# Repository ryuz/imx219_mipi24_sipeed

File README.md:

# Tang Mega 138K Pro Dock 用 IMX219 MIPI 変換基板

[English version is here (README_en.md)](README_en.md)

## 概要

[Raspberry Pi Camera V2](https://raspberry-pi.ksyic.com/main/index/pdp.id/144/pdp.open/144) のベース基板を入れ替えて、Sipeed さんの [Tang Mega 138K Pro Dock](https://wiki.sipeed.com/hardware/en/tang/tang-mega-138k/mega-138k-pro.html) に繋ぐための変換基板です。

おそらく Sipeed さんの独自仕様と思われる 24pin の MIPI コネクタで Sonyさんの IMX219 センサーを利用可能にします。

## 変換基板のイメージ

下記のような変換基板です。

Raspberry Pi Camera V2 カメラから、カメラモジュール部分を取り外して、この変換基板に取り付けることで、利用します。

実際に取り付けたのが下記の写真です。

## 各種データ

回路図は下記の通りです(pdf版は[こちら](imx219_mipi24/imx219_mipi24.pdf))です。

[KiCAD](https://www.kicad.org/) version 9.0.0 で設計しております。

[JLCPCB](https://jlcpcb.com/) さんの４層基板で「FR4-Standard TG 135-140」の製造仕様に合わせてインピーダンスコントロールしております。

手元での試作は JLCPCBさんの PCBA で行っており、たまたま在庫表示のあった部品を選定したこともあり、発信器などでディスコン品番なども混ざっておりますが、各自で製造される場合は必要に応じて後継の互換品を選定ください。

ケーブルは[05-24-A-0030-A-4-06-4-T](https://www.marutsu.co.jp/pc/i/46064636/) と [05-24-A-0152-A-4-06-4-T](https://www.marutsu.co.jp/pc/i/46064715/) の2種類で試しております。

## 動作テスト

下記のプロジェクトなどで動作テストを行っております。

- https://github.com/ryuz/jelly/tree/master/projects/tang_mega_138k_pro/tang_mega_138k_pro_imx219_720p
- https://github.com/ryuz/jelly/tree/master/projects/tang_mega_138k_pro/tang_mega_138k_pro_imx219_stereo

実際に2つのカメラを繋いで、256x256 の画像を交互に表示したいるのが下記です。

なお単純な受信テストは 2lane と 4lane の両方ともうまくいっております。

## 免責事項

本設計データは、研究開発用の試作実験に用するものであり、利用に際して発生した如何なる損害も作者は補償いたしませんので予めご了承ください。

## BOOTH への出品

自身で基板製造するのが難しい方の為に、作者が少し余分に製造したものを [BOOTH](https://rtc-lab.booth.pm/) に出品しております。

- [Tang Mega 138K Pro Dock 用 IMX219 MIPI 変換基板](https://rtc-lab.booth.pm/items/7095235)
- [Tang Mega 138K Pro Dock 用 IMX219 MIPI カメラ基板(イメージセンサー付き)](https://rtc-lab.booth.pm/items/7132890)

あくまで試作品ですので品質を保証できるものではなく、在庫限りとなりますが、よろしければご活用ください。

当方からご購入いただいた基板に関しては商用/非商用ともに自由にお使いいただけます。
購入品の商用利用の為に回路図のみ別途[こちら](https://github.com/ryuz/imx219_mipi24_sipeed_schematic)でMITライセンスでも公開しております。

## ライセンス(License)

本設計データは、[クリエイティブ・コモンズ 表示-非営利 4.0 国際 ライセンス](https://creativecommons.org/licenses/by-nc/4.0/deed.ja)の下で提供されています。

製造した本基板の販売や配布を行わない限りは、趣味や研究開発用途でご自由にお使いいただく事が出来ます。
また、商用に製造販売を希望される場合は、別途ライセンス契約を作者までご相談ください。

## 作者情報

渕上 竜司(Ryuji Fuchikami)
[リアルタイムコンピューティング研究所](https://rtc-lab.com/)

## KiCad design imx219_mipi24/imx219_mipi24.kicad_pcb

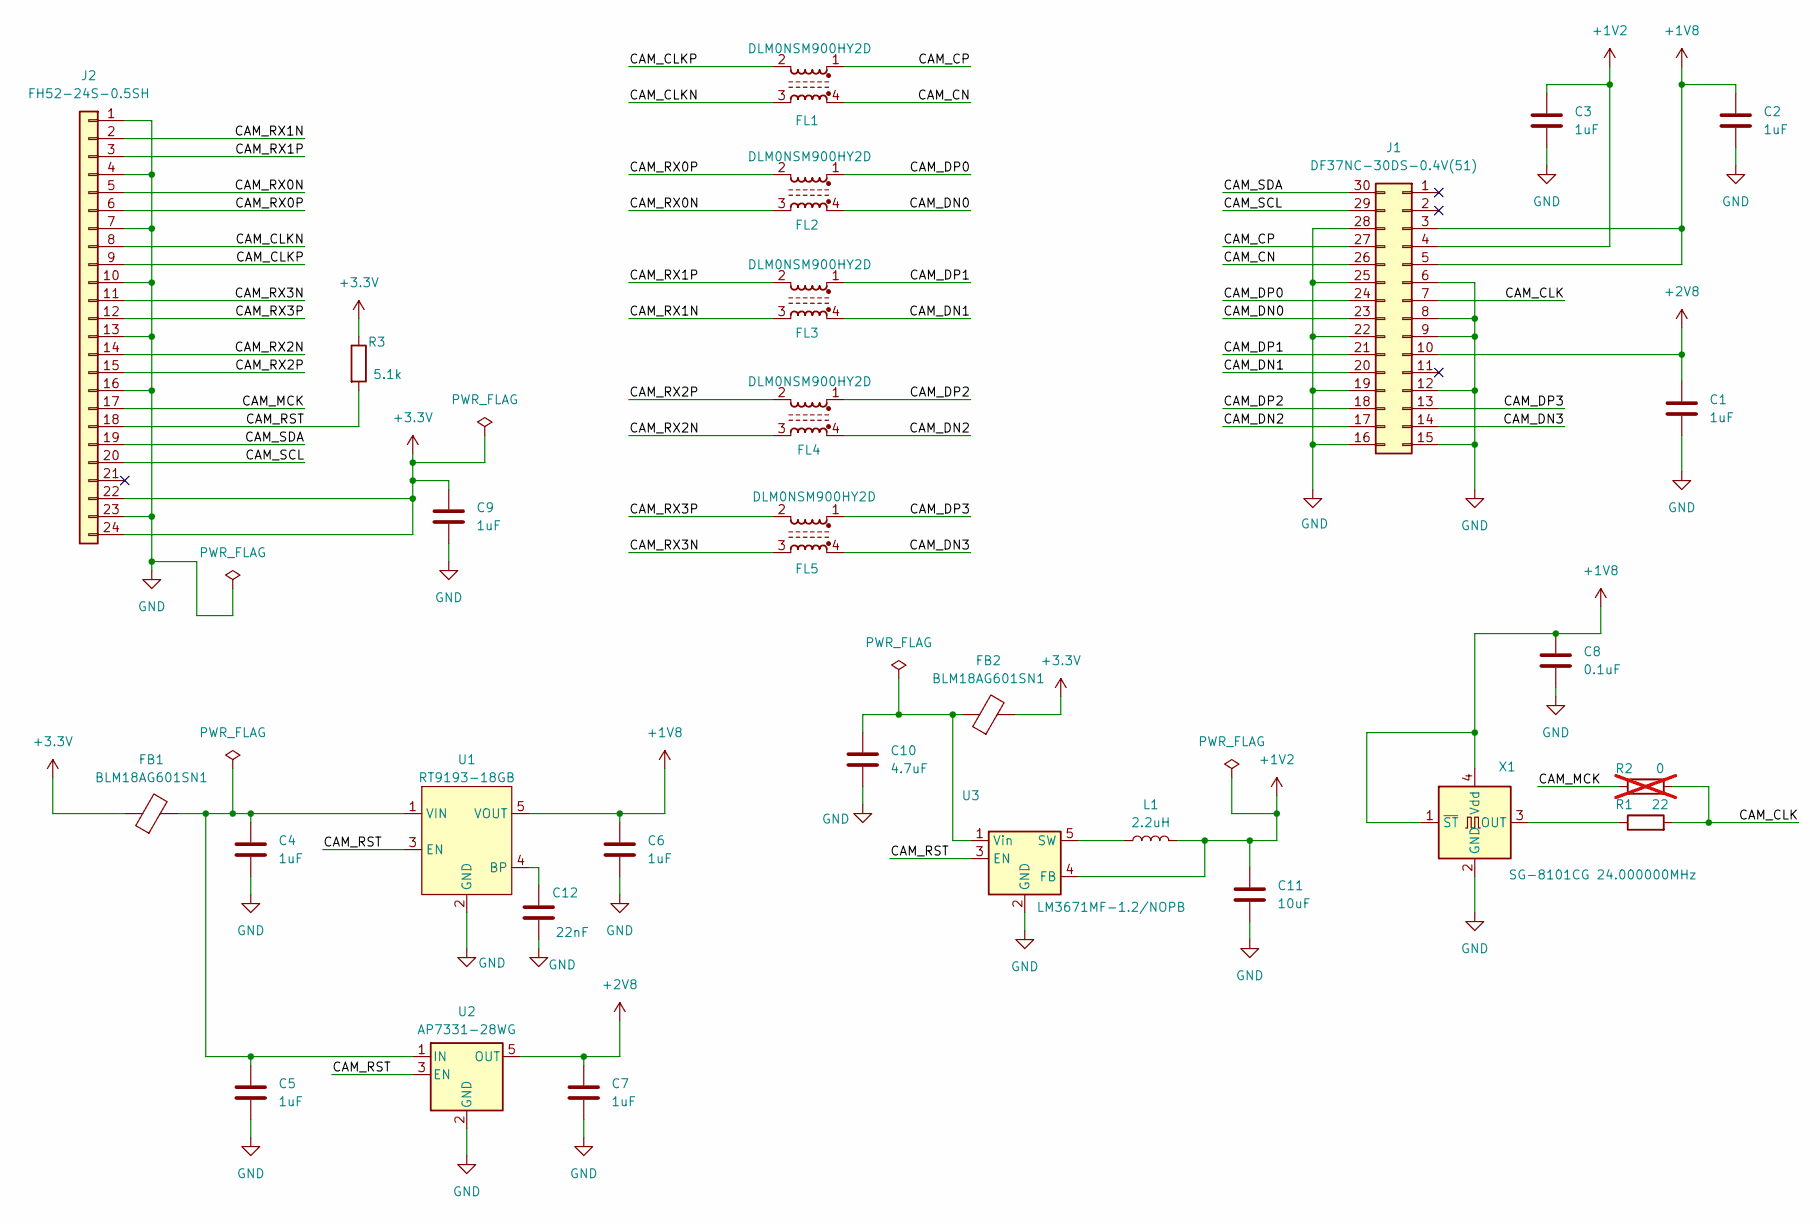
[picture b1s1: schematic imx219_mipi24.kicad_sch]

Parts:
C1, C2, C3, C4, C5, C6, C7, C9: 1uF; C_0402_1005Metric
C8: 0.1uF; C_0402_1005Metric
C10: 4.7uF; C_0603_1608Metric
C11: 10uF; C_0603_1608Metric
C12: 22nF; C_0402_1005Metric
FB1, FB2: BLM18AG601SN1; L_0603_1608Metric; JLC C19330
FL1, FL2, FL3, FL4, FL5: DLM0NSM900HY2D; JLC C1857796
J1: DF37NC-30DS-0.4V(51); HRS_DF37NC-30DS-0.4V_51; JLC C424634
J2: FH52-24S-0.5SH; JLC C5378714
L1: 2.2uH; L_1008_2520Metric; JLC C5832372
R1: 22; R_0402_1005Metric
R2: 0; R_0402_1005Metric; not fitted
R3: 5.1k; R_0402_1005Metric
U1: RT9193-18GB; SOT-23-5; JLC C27416
U2: AP7331-28WG; SOT25; JLC C460376
U3: LM3671MF-1.2/NOPB; TSOT-23-5; JLC C2650333
X1: SG-8101CG 24.000000MHz; SG-8101CG; JLC C390546

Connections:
+1V2: C3.1, C11.1, J1.4, L1.2, U3.4 (FB)
+1V8: C2.1, C6.1, C8.1, J1.3, J1.5, U1.5 (VOUT), X1.1 (~ST), X1.4 (Vdd)
+2V8: C1.1, C7.1, J1.10, U2.5 (OUT)
+3.3V: C9.1, FB1.1, FB2.2, J2.22, J2.24, R3.1
/CAM_CLK: J1.7, R1.2, R2.2
/CAM_CLKN: FL1.3, J2.8
/CAM_CLKP: FL1.2, J2.9
/CAM_CN: FL1.4, J1.26
/CAM_CP: FL1.1, J1.27
/CAM_DN0: FL2.4, J1.23
/CAM_DN1: FL3.4, J1.20
/CAM_DN2: FL4.4, J1.17
/CAM_DN3: FL5.4, J1.14
/CAM_DP0: FL2.1, J1.24
/CAM_DP1: FL3.1, J1.21
/CAM_DP2: FL4.1, J1.18
/CAM_DP3: FL5.1, J1.13
/CAM_MCK: J2.17, R2.1
/CAM_RST: J2.18, R3.2, U1.3 (EN), U2.3 (EN), U3.3 (EN)
/CAM_RX0N: FL2.3, J2.5
/CAM_RX0P: FL2.2, J2.6
/CAM_RX1N: FL3.3, J2.2
/CAM_RX1P: FL3.2, J2.3
/CAM_RX2N: FL4.3, J2.14
/CAM_RX2P: FL4.2, J2.15
/CAM_RX3N: FL5.3, J2.11
/CAM_RX3P: FL5.2, J2.12
/CAM_SCL: J1.29, J2.20
/CAM_SDA: J1.30, J2.19
GND: C1.2, C2.2, C3.2, C4.2, C5.2, C6.2, C7.2, C8.2, C9.2, C10.2, C11.2, C12.2, J1.6, J1.8, J1.9, J1.12, J1.15, J1.16, J1.19, J1.22, J1.25, J1.28, J2.1, J2.4, J2.7, J2.10, J2.13, J2.16, J2.23, U1.2 (GND), U2.2 (GND), U3.2 (GND), X1.2 (GND)
unnamed: C12.1, U1.4 (BP)
unnamed: C4.1, C5.1, FB1.2, U1.1 (VIN), U2.1 (IN)
unnamed: L1.1, U3.5 (SW)
unnamed: C10.1, FB2.1, U3.1 (Vin)
unnamed: R1.1, X1.3 (OUT)

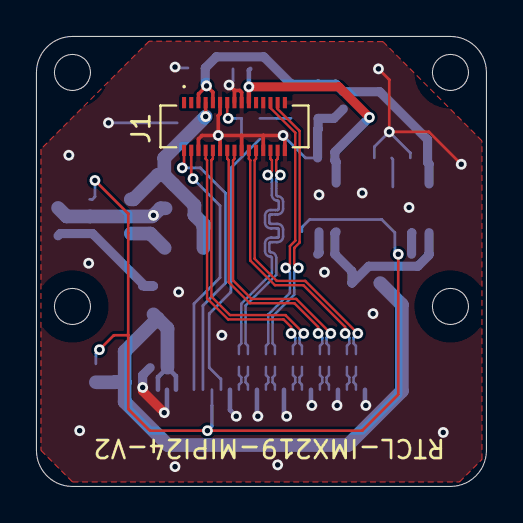
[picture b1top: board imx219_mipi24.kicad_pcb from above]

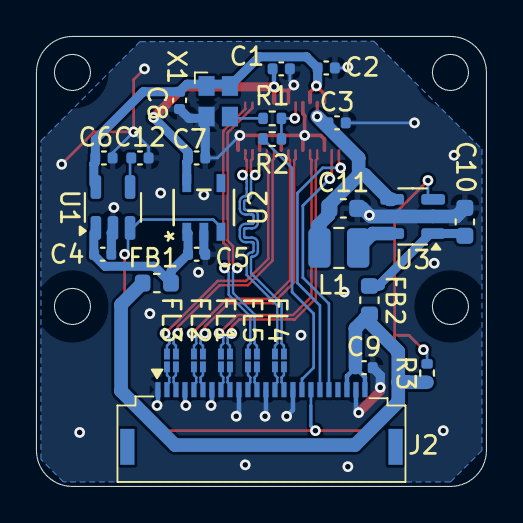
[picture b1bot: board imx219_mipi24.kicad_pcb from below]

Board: 4 copper layers, 25.0 x 25.0 mm, 29 parts (28 on the bottom side), 35 nets.

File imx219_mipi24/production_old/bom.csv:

Designator,Footprint,Quantity,Value,LCSC Part #
"C1, C2, C3, C4, C5, C6, C7, C9",0402,8,1uF,
C10,0603,1,4.7uF,
C11,0603,1,10uF,
C12,0402,1,22nF,
C8,0402,1,0.1uF,
"FB1, FB2",0603,2,BLM18AG601SN1,C19330
"FL1, FL2, FL3, FL4, FL5",DLM0NSM900HY2D,5,DLM0NSM900HY2D,C1857796
J1,HRS_DF37NC-30DS-0.4V_51,1,DF37NC-30DS-0.4V(51),C424634
J2,FH52-24S-0.5SH,1,FH52-24S-0.5SH,C5378714
L1,1008,1,2.2uH,C5832372
R1,0402,1,22,
R3,0402,1,5.1k,
U1,SOT-23-5,1,RT9193-18GB,C27416
U2,SOT25,1,AP7331-28WG,C460376
U3,TSOT-23-5,1,LM3671MF-1.2/NOPB,C2650333
X1,SG-8101CG,1,SG-8101CG 24.000000MHz,C390546

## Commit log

2025-05-10 1st commit
2025-05-24 Add 3D models for SG-8101CG and SOT25 footprints
2025-05-24 update pdf
2025-05-27 Update README_en.md
    I hope that helps.
2025-07-06 add stereo_view. image
